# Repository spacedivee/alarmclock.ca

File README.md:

# Alarmclock.ca , A canadian outdoor designed alarm clock

A custom-built digital alarm clock made for the [BLARE project by Hack Club](https://blare.hackclub.com/). 

## Overview

The goal of this project is to build a functional alarm clock using the BLARE kit, with a focus on embedded firmware, electronics integration, and mechanical design.

The clock is designed to display the current time and allow the user to configure and use an alarm. A rotary encoder provides an additional input method ( like to quickly change the time or navigate a menu quicker) , while a piezo buzzer provides the alarm sound.

The case and other systems were designed for outdoor/camping use.

## Features

- Digital clock displayed on a TFT screen.
- Alarm functionality with an audible buzzer.
- Rotary encoder for user input and navigation.
- Auxiliary battery pack with a physical power switch. (when not plugged in)
- A simple hook at the top to attach the clock to other things
- Slots for plexiglass or other transparent material to be attached to protect the TFT screen. 

## Project Photos

### Assembled Clock

*ill drop it once i actually get it and build it*

### Schematic

### PCB Design

*The PCB as seen on KiCad*

*The 3D Model*

### Enclosure and Assembly

*Full Build Assembly*

*Case Body*

*Lid*

## Hardware

The project uses the following components.

| Component | Purpose |
|---|---|
| Seeed XIAO ESP32C3 | Main microcontroller |
| 2.25-inch ST7789 TFT display | Displays the clock interface |
| 3.3 V piezo buzzer | Produces the alarm sound |
| Rotary encoder | User input |
| Auxiliary battery pack | Portable power supply |
| Physical power switch | Controls power to the clock |
| Custom PCB | Connects the electronic components |
| Custom enclosure | Houses and protects the assembly |

The BLARE kit also includes keyboard switches, keycaps, diodes, display headers, jumper wires, heat-set inserts, and mounting screws.

## Bill of Materials (BOM)

| Part | Quantity | Source |
|---|---:|---|
| Seeed XIAO ESP32C3 | 1 | BLARE kit |
| ST7789 TFT display | 1 | BLARE kit |
| 3.3 V piezo buzzer | 1 | BLARE kit |
| MX-style keyboard switches | 4 | BLARE kit |
| White DSA keycaps | 4 | BLARE kit |
| Display header and jumper wires | 1 | BLARE kit |
| Rotary encoder | 1 | Provided by me |
| Auxiliary battery pack | 1 | Provided by me |
| Power switch | 1 | Provided by me |
| Custom PCB | 1 | Designed in KiCad |

*The BOM lists the supplied kit components and additional hardware.*

## Firmware

The firmware is developed in the Arduino IDE for the Seeed XIAO ESP32C3.

To be implemented: sleep mode or something of the sort that reduces battery usage when not in use.
Add the license you choose for your firmware, PCB design, and CAD files. Make sure the license is appropriate for any third-party libraries or design assets included in the project.

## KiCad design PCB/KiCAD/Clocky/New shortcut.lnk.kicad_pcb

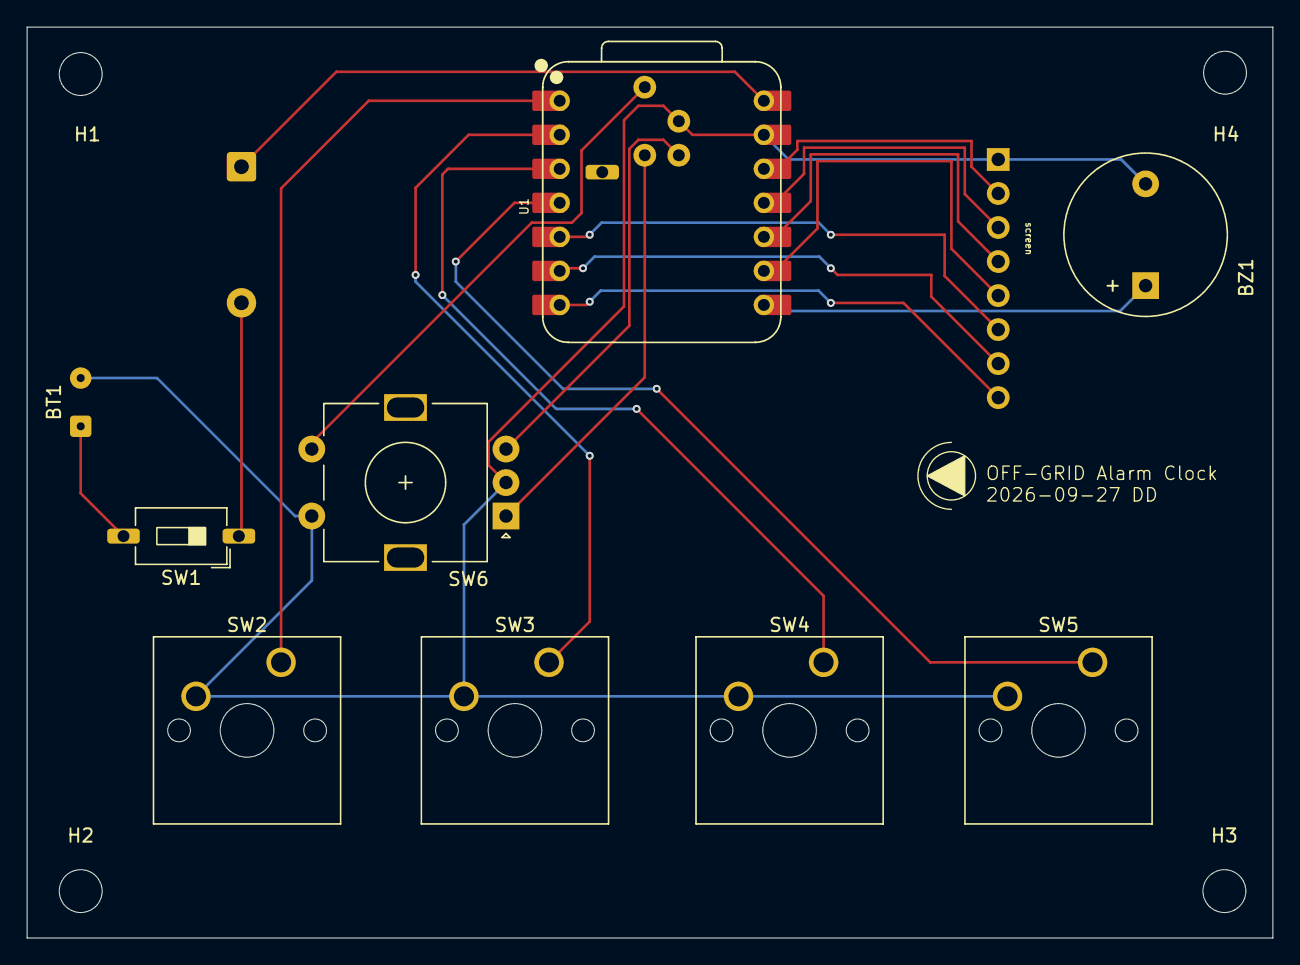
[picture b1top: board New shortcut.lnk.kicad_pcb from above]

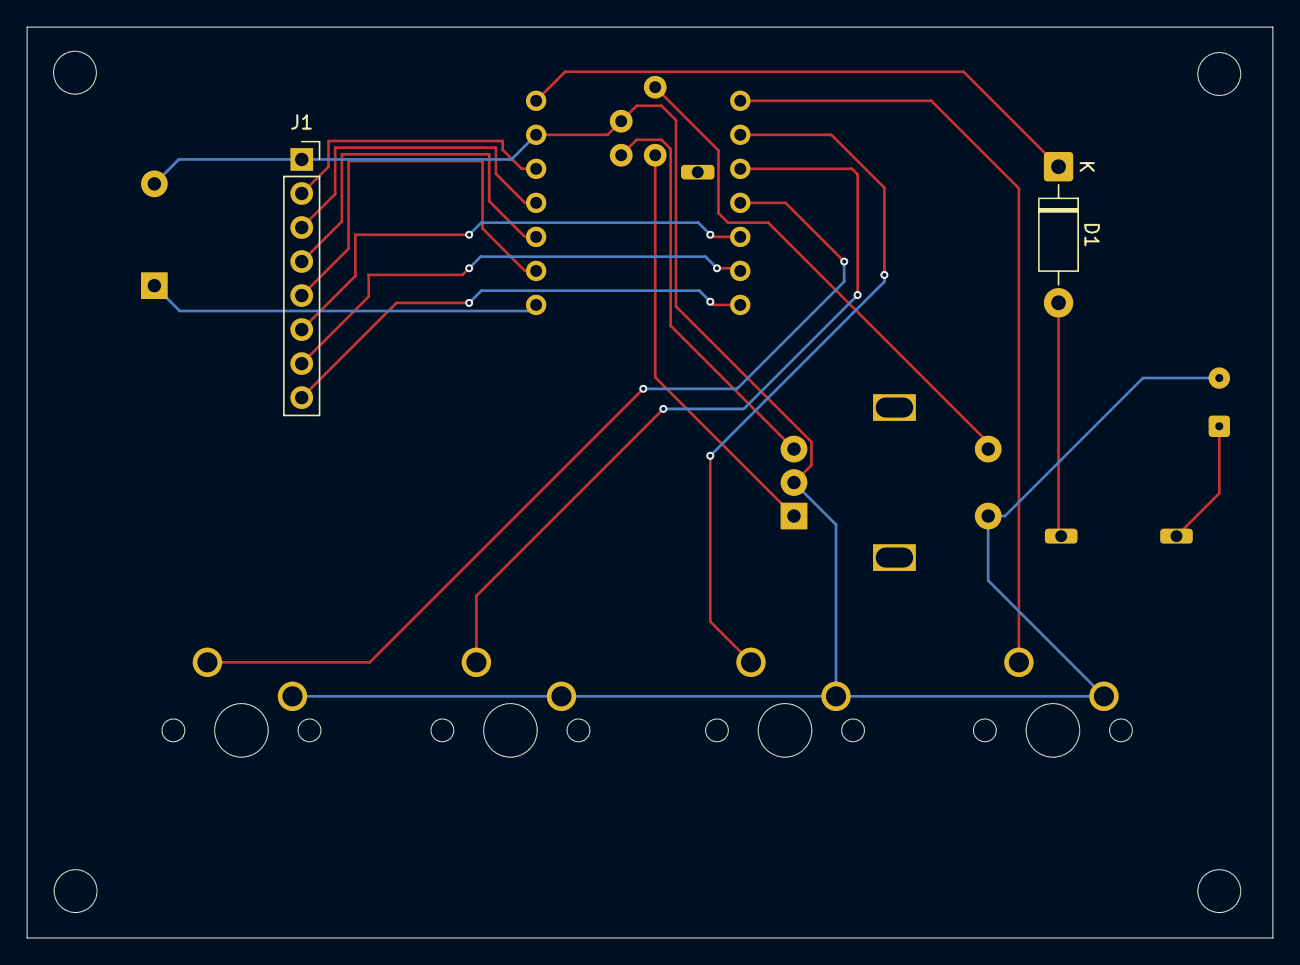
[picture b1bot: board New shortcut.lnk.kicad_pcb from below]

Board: 2 copper layers, 93.0 x 68.0 mm, 15 parts (2 on the bottom side), 19 nets.

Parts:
BT1: Battery; SolderWire-0.1sqmm_1x02_P3.6mm_D0.4mm_OD1mm
BZ1: Buzzer; Buzzer_12x9.5RM7.6
D1: D_Schottky; D_DO-41_SOD81_P10.16mm_Horizontal
H1, H2, H3, H4: MountingHole; MountingHole_3.2mm_M3
J1: Conn_01x08_Pin; PinSocket_1x08_P2.54mm_Vertical
SW1: SW_DPST_x2; SW_DIP_SPSTx01_Slide_6.7x4.1mm_W8.61mm_P2.54mm_LowProfile
SW2, SW3, SW4, SW5: SW_Push; SW_Cherry_MX_1.00u_PCB
SW6: RotaryEncoder_Switch; RotaryEncoder_Alps_EC11E-Switch_Vertical_H20mm
U1: XIAO-ESP32-C3-SMD; XIAO-ESP32-C3-DIP-SMD

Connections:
+3.3V: J1.2, U1.12 (3V3_OUT)
/BL: J1.8, U1.7 (D6)
/CS: J1.7, U1.6 (D5)
/DC: J1.6, U1.5 (D4)
/RST: J1.5, U1.9 (D8)
/SCL: J1.3, U1.11 (D10)
/SDA: J1.4, U1.10 (D9/BOOT)
GND: BT1.2 (-), BZ1.2 (-), J1.1, SW2.2, SW3.2, SW4.2, SW5.2, SW6.C, SW6.S2, U1.13 (GND), U1.18 (GND)
unnamed: BT1.1 (+), SW1.2 (B)
unnamed: BZ1.1 (+), U1.8 (D7)
unnamed: D1.2 (A), SW1.1 (A)
unnamed: D1.1 (K), U1.14 (VBUS)
unnamed: SW2.1, U1.1 (D0)
unnamed: SW3.1, U1.2 (D1)
unnamed: SW4.1, U1.3 (D2)
unnamed: SW6.A, U1.19 (D2/MTMS)
unnamed: SW5.1, U1.4 (D3)
unnamed: SW6.S1, U1.15 (D3/MTDI)
unnamed: SW6.B, U1.20 (D4/MTCK)
